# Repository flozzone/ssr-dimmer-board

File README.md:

# ssr-dimmer-board

Rebuild of https://github.com/fleshgordo/diskohedron using recent 
SSRs with source code for Arduino microcontroller.

## Hardware

* Schematic: https://github.com/flozzone/ssr-dimmer-board/blob/master/hw/schematic.pdf
* Layout: https://github.com/flozzone/ssr-dimmer-board/blob/master/hw/layout.pdf

## Building

    # prepare build framework
    cd src
    ./configure
    
    # building arduino v3.1 firmware
    cd bin-firmware
    make
    cd ..

    # building client library
    cd bin-client
    make
    cd ..
    
## Uploading

After having run through the building process you can upload the firmware
to the arduino. Be sure to attach the arduino with an USB cable to the 
workstation (It should be recognized as /dev/ttyUSB0).

    cd src/bin-firmware
    make upload
    
## Pin-Mapping

| Pin name 	| Description      	| Type (AVR side) 	| Arduino Pin   	| AVR Pin 	|
|----------	|------------------	|-----------------	|---------------	|---------	|
| ZC       	| Zero cross       	| INPUT           	| digital pin 2 	| PD2     	|
| CH1      	| Channel1 control 	| OUTPUT          	| digital pin 4 	| PD4     	|
| CH2      	| Channel2 control 	| OUTPUT          	| digital pin 5 	| PD5     	|
| CH3      	| Channel3 control 	| OUTPUT          	| digital pin 6 	| PD6     	|
| CH4      	| Channel4 control 	| OUTPUT          	| digital pin 7 	| PD7     	|
| CH5      	| Channel5 control 	| OUTPUT          	| digital pin 8 	| PB0     	|
| GND      	| Ground           	| POWER           	| GND           	| GND     	|

## Serial Protocol

The serial protocol consists of one single 5 byte message, which is described
in the following struct message. 

For the value argument of the message, currently only values between 0 and 16
are allowed.

    struct message {
      byte magic1 = 0xF6;
      byte magic2 = 0x6F;
      enum e_fire_type fire_type;
      enum e_channels channel_nr;
      byte value;
    };

    enum e_fire_type {
        NO_FIRE,
        PHASE_TRAILING_EDGE,
        PHASE_LEADING_EDGE,
        FULL_WAVE_BURST,
        HALF_WAVE_BURST
    };

    enum e_channels {
        CHANNEL1 = 0,
        CHANNEL2,
        CHANNEL3,
        CHANNEL4,
        CHANNEL5
    };

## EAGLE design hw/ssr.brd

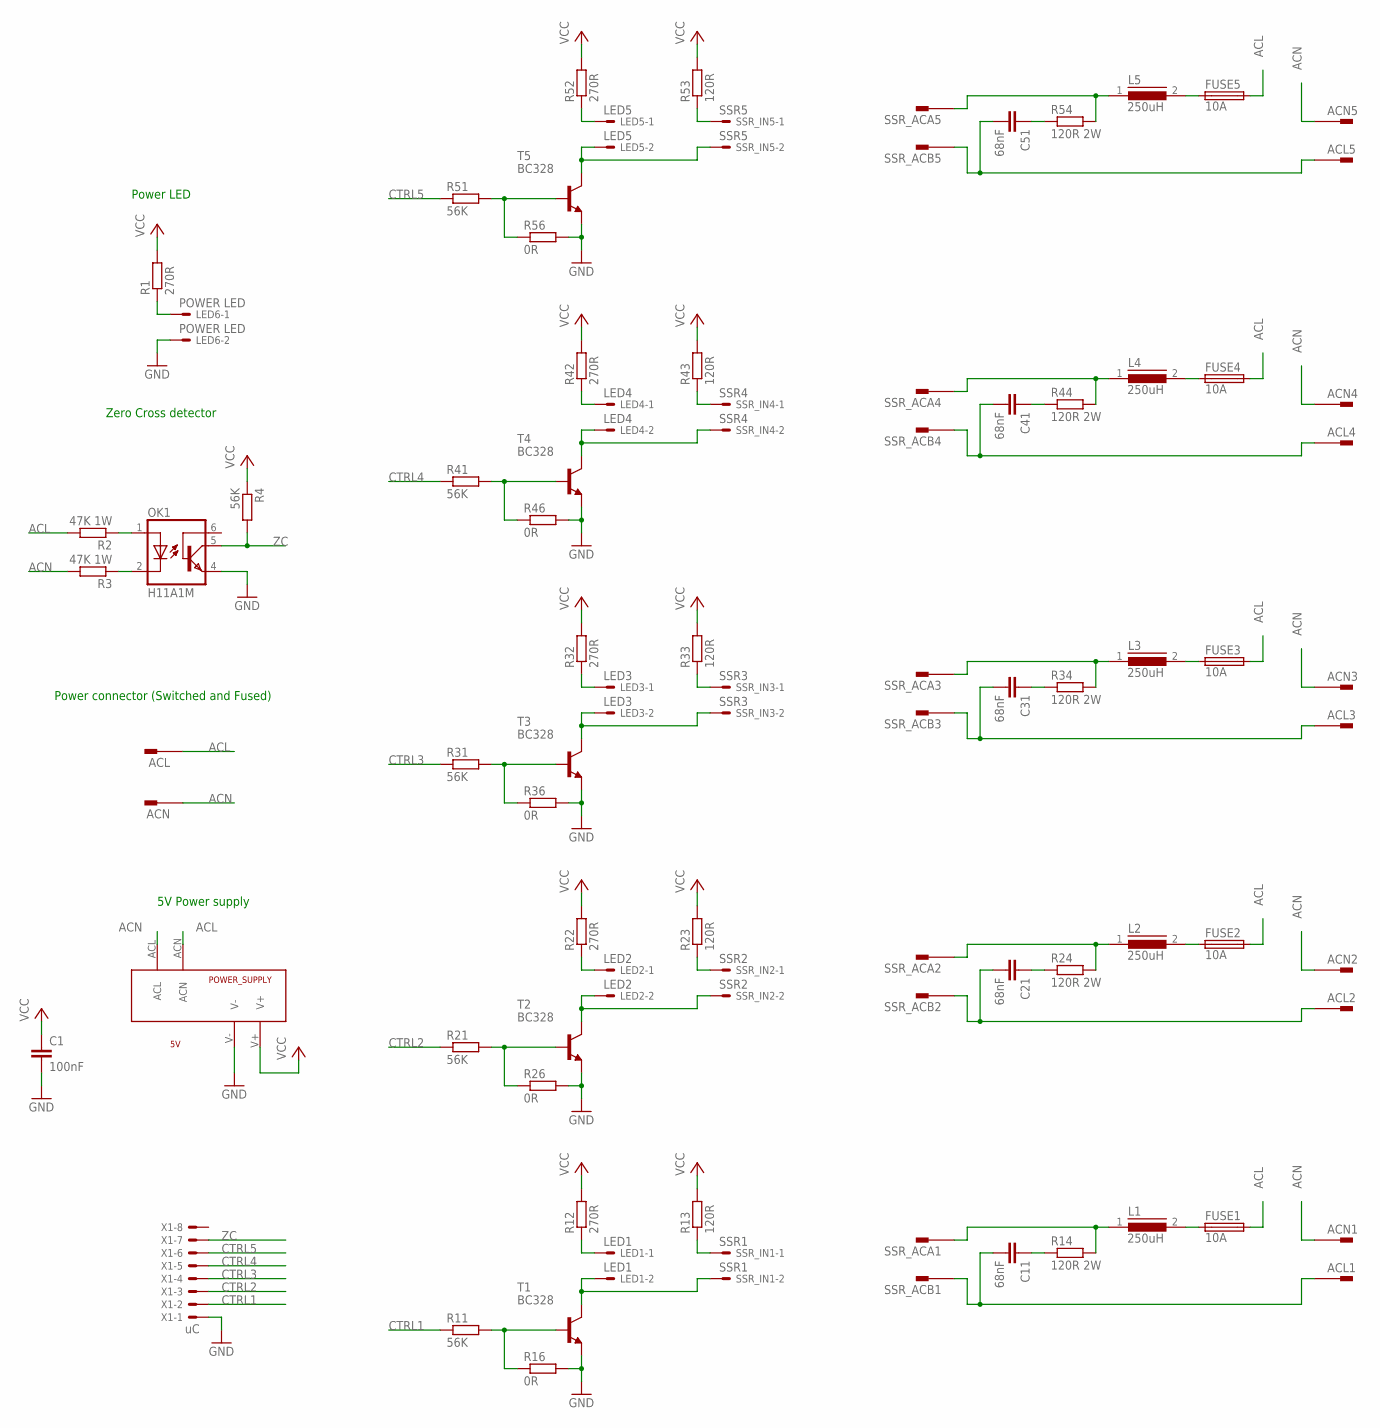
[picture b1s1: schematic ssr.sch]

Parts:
ACL, ACL1, ACL2, ACL3, ACL4, ACL5: PIN2F061.080; F061.080
ACN, ACN1, ACN2, ACN3, ACN4, ACN5: PIN2F061.080; F061.080
C1: 100nF; C2.5-2
C11, C21, C31, C41, C51: 68nF; C150-054X183
FUSE1, FUSE2, FUSE3, FUSE4, FUSE5: 10A; SH22,5
L1, L2, L3, L4, L5: 250uH; ATCA-08
LED1: LED1; KK-156-2
LED2: LED2; KK-156-2
LED3: LED3; KK-156-2
LED4: LED4; KK-156-2
LED5: LED5; KK-156-2
LED6: POWER LED; KK-156-2
OK1: H11A1M; DIL06
POWER_SUPPLY: 5V; SPN00205
R1, R12, R22, R32, R42, R52: 270R; 0207/10
R2, R3: 47K 1W; 0309/12
R4, R11, R21, R31, R41, R51: 56K; 0207/10
R13, R23, R33, R43, R53: 120R; 0207/10
R14, R24, R34, R44, R54: 120R 2W; 0617/22
R16, R26, R36, R46, R56: 0R; 0207/10
SSR_ACA1, SSR_ACA2, SSR_ACA3, SSR_ACA4, SSR_ACA5: PIN2F061.080; F061.080
SSR_ACB1, SSR_ACB2, SSR_ACB3, SSR_ACB4, SSR_ACB5: PIN2F061.080; F061.080
SSR_IN1: SSR1; KK-156-2
SSR_IN2: SSR2; KK-156-2
SSR_IN3: SSR3; KK-156-2
SSR_IN4: SSR4; KK-156-2
SSR_IN5: SSR5; KK-156-2
T1, T2, T3, T4, T5: BC328; TO92
X1: uC; KK-156-8

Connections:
ACL: ACL.1A, ACL.1B, FUSE1.2, FUSE2.2, FUSE3.2, FUSE4.2, FUSE5.2, POWER_SUPPLY.ACN, R2.2
ACN: ACN.1A, ACN.1B, ACN1.1A, ACN1.1B, ACN2.1A, ACN2.1B, ACN3.1A, ACN3.1B, ACN4.1A, ACN4.1B, ACN5.1A, ACN5.1B, POWER_SUPPLY.ACL, R3.2
CTRL1: R11.1, X1.2
CTRL2: R21.1, X1.3
CTRL3: R31.1, X1.4
CTRL4: R41.1, X1.5
CTRL5: R51.1, X1.6
GND: C1.2, LED6.2, OK1.4 (EMI), POWER_SUPPLY.V-, R16.2, R26.2, R36.2, R46.2, R56.2, T1.1 (E), T2.1 (E), T3.1 (E), T4.1 (E), T5.1 (E), X1.1
unnamed: LED1.2, SSR_IN1.2, T1.3 (C)
unnamed: LED1.1, R12.1
unnamed: R13.1, SSR_IN1.1
unnamed: R11.2, R16.1, T1.2 (B)
unnamed: C11.1, R14.1
unnamed: OK1.2 (C), R3.1
unnamed: OK1.1 (A), R2.1
unnamed: R23.1, SSR_IN2.1
unnamed: LED2.1, R22.1
unnamed: R21.2, R26.1, T2.2 (B)
unnamed: C21.1, R24.1
unnamed: LED2.2, SSR_IN2.2, T2.3 (C)
unnamed: R33.1, SSR_IN3.1
unnamed: LED3.1, R32.1
unnamed: R31.2, R36.1, T3.2 (B)
unnamed: C31.1, R34.1
unnamed: LED3.2, SSR_IN3.2, T3.3 (C)
unnamed: R43.1, SSR_IN4.1
unnamed: LED4.1, R42.1
unnamed: R41.2, R46.1, T4.2 (B)
unnamed: C41.1, R44.1
unnamed: LED4.2, SSR_IN4.2, T4.3 (C)
unnamed: R53.1, SSR_IN5.1
unnamed: LED5.1, R52.1
unnamed: R51.2, R56.1, T5.2 (B)
unnamed: C51.1, R54.1
unnamed: LED5.2, SSR_IN5.2, T5.3 (C)
unnamed: LED6.1, R1.1
unnamed: FUSE5.1, L5.2
unnamed: FUSE4.1, L4.2
unnamed: FUSE3.1, L3.2
unnamed: FUSE2.1, L2.2
unnamed: FUSE1.1, L1.2
SSR_ACA1: L1.1, R14.2, SSR_ACA1.1A, SSR_ACA1.1B
SSR_ACA2: L2.1, R24.2, SSR_ACA2.1A, SSR_ACA2.1B
SSR_ACA3: L3.1, R34.2, SSR_ACA3.1A, SSR_ACA3.1B
SSR_ACA4: L4.1, R44.2, SSR_ACA4.1A, SSR_ACA4.1B
SSR_ACA5: L5.1, R54.2, SSR_ACA5.1A, SSR_ACA5.1B
SSR_ACB1: ACL1.1A, ACL1.1B, C11.2, SSR_ACB1.1A, SSR_ACB1.1B
SSR_ACB2: ACL2.1A, ACL2.1B, C21.2, SSR_ACB2.1A, SSR_ACB2.1B
SSR_ACB3: ACL3.1A, ACL3.1B, C31.2, SSR_ACB3.1A, SSR_ACB3.1B
SSR_ACB4: ACL4.1A, ACL4.1B, C41.2, SSR_ACB4.1A, SSR_ACB4.1B
SSR_ACB5: ACL5.1A, ACL5.1B, C51.2, SSR_ACB5.1A, SSR_ACB5.1B
VCC: C1.1, POWER_SUPPLY.V+, R1.2, R4.1, R12.2, R13.2, R22.2, R23.2, R32.2, R33.2, R42.2, R43.2, R52.2, R53.2
ZC: OK1.5 (COL), R4.2, X1.7

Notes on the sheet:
Power connector (Switched and Fused)
5V Power supply
Zero Cross detector
Power LED

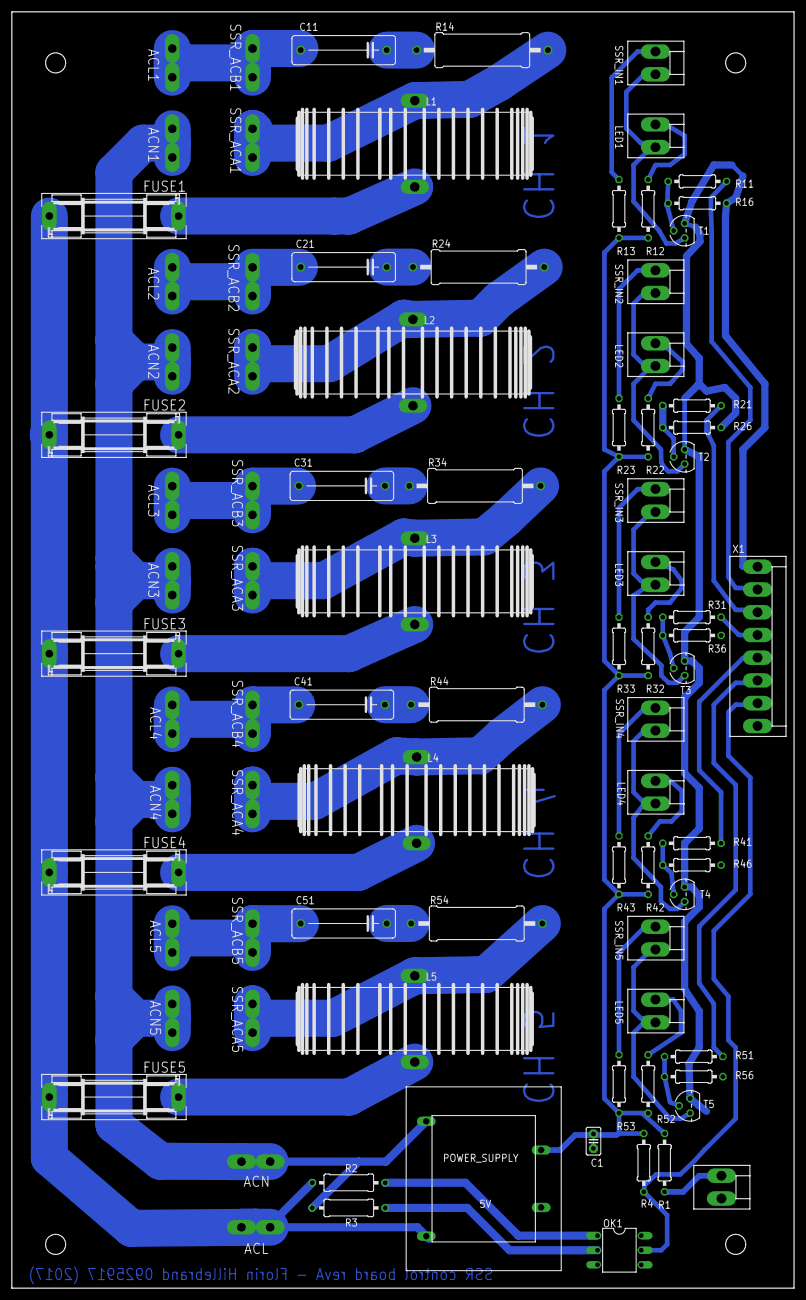
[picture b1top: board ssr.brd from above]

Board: 2 copper layers, 136.2 x 222.2 mm, 87 parts (0 on the bottom side), 53 nets.

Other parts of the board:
DRILEGEND: DRILEGEND

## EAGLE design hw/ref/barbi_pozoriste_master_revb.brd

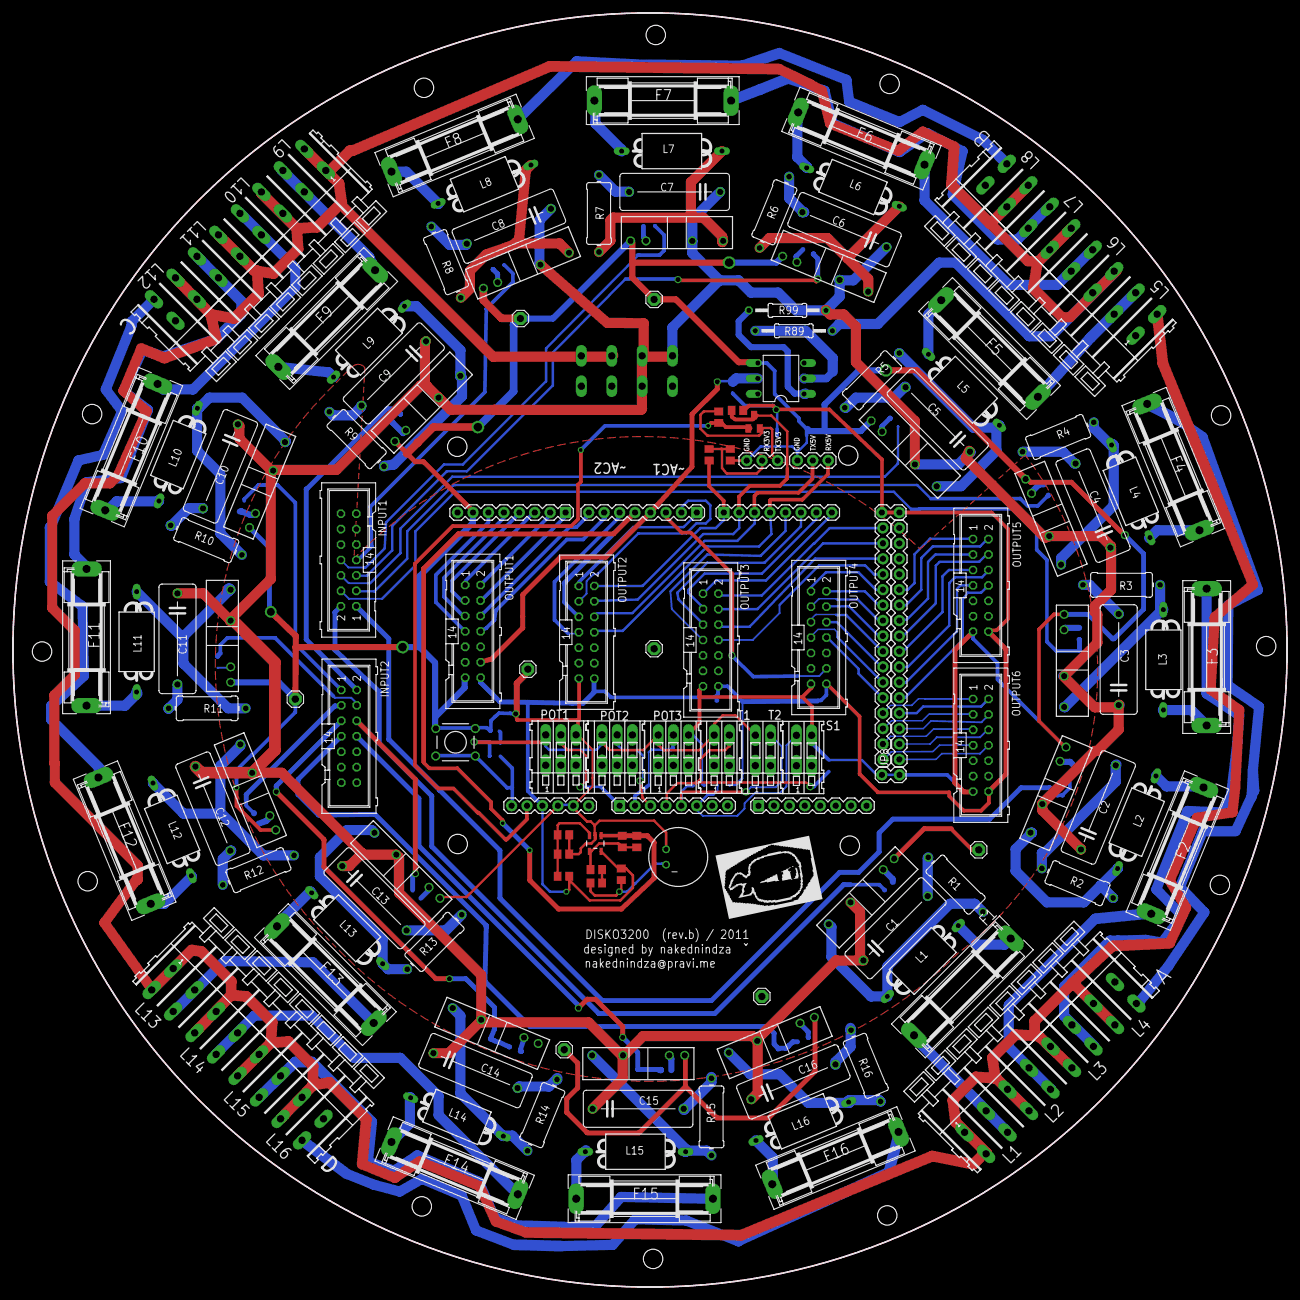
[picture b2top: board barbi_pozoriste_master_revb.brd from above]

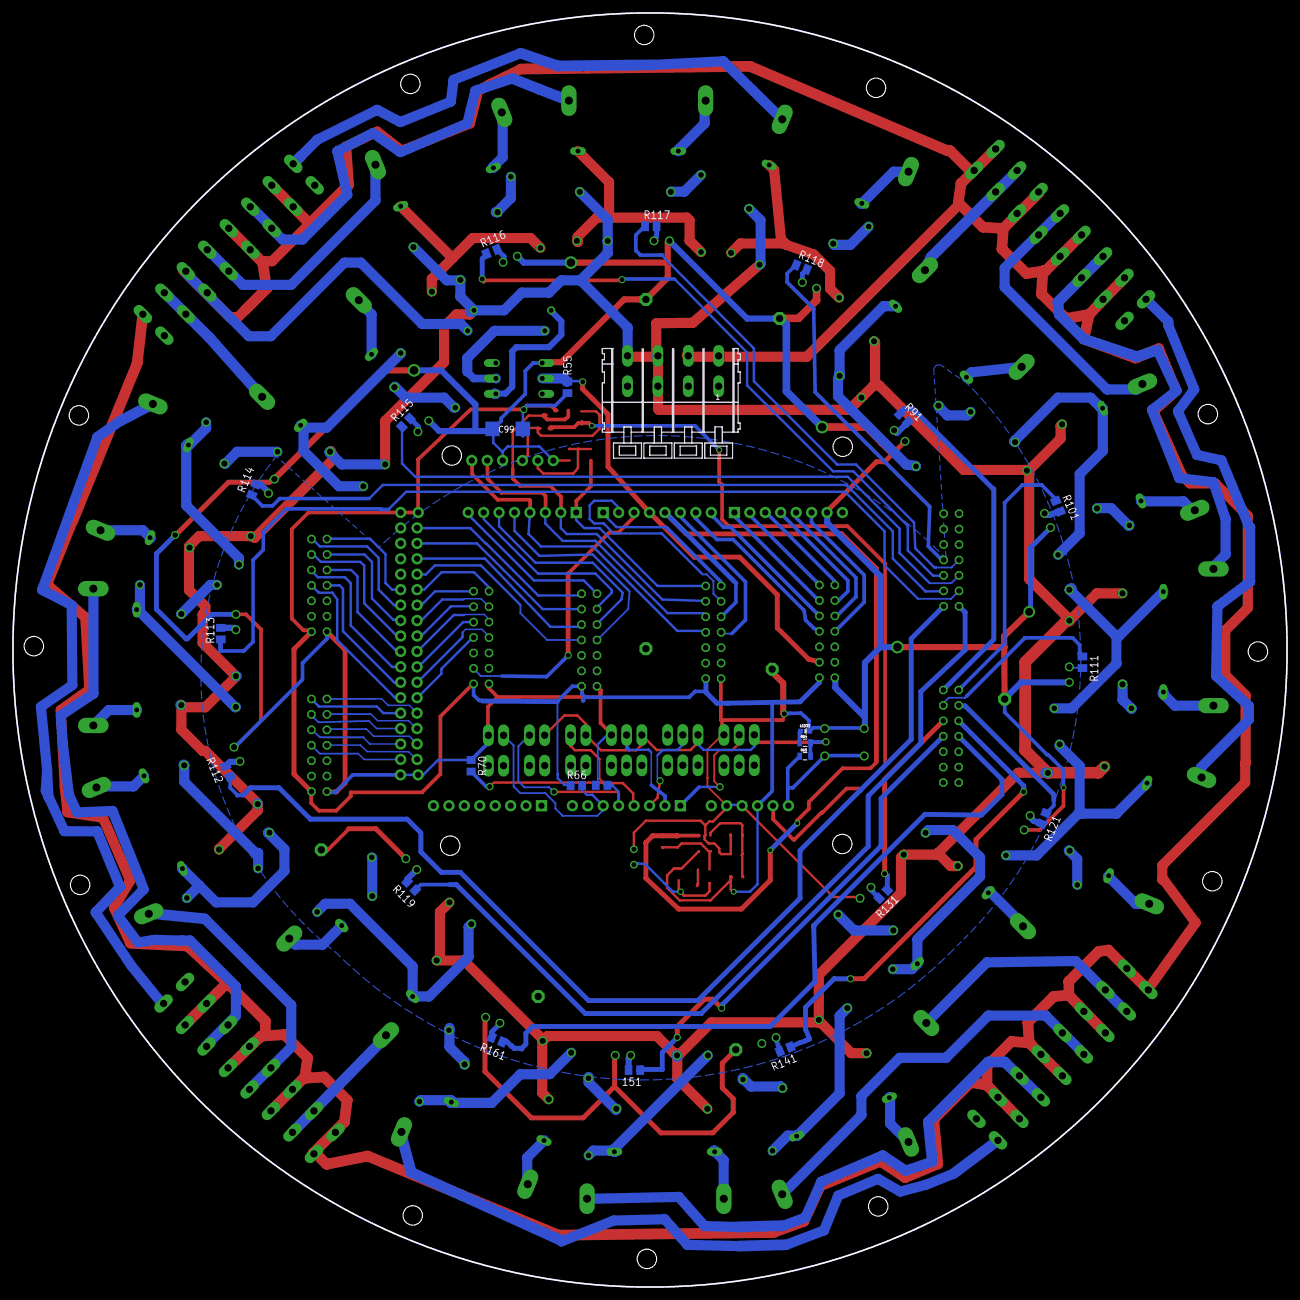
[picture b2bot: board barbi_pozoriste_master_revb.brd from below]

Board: 2 copper layers, 209.7 x 209.7 mm, 162 parts (25 on the bottom side), 168 nets.

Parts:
151: 330R; M0805
C1, C2, C3, C4, C5, C6, C7, C8, C9, C10, C11, C12, C13, C14, C15, C16: 68nF; C150-064X183
C17: 4.7uF; C0805
C18: 12pF; C0805
C19: 1uF; C0805
C99: 47uF; SMC_C
F1, F2, F3, F4, F5, F6, F7, F8, F9, F10, F11, F12, F13, F14, F15, F16: 3A; SH22,5
JP1, JP2: 1X03
JP3, JP4, JP5, JP6, JP7: 1X08
JP8, JP9: M16PTH; 1X16
JP10: 1X06
JP11, JP12: 1X02_LOCK
K1, K2, K3, K4, K5, K6, K7, K8, K9, K10, K11, K12, K13, K14, K15, K16: S202S01; S102S01
L1, L2, L3, L4, L5, L6, L7, L8, L9, L10, L11, L12, L13, L14, L15, L16: 300uH; ZD6-2W5
LED33: Red; LED-0603
LSP1, LSP2, LSP3, LSP4, LSP5, LSP6, LSP7, LSP8: MCS08
OK1: H11A1M; DIL06
Q1: BSS123; SOT23
R1, R2, R3, R4, R5, R6, R7, R8, R9, R10, R11, R12, R13, R14, R15, R16: 120R 2W; 0411/12
R17: 2k2; R0805
R18, R19, R20, R21, R22, R24, R25, R70, R71: 10k; R0805
R23: 1M; R0805
R55: 10k; M0805
R64: 330; 0805
R65: 10k; 0805
R66: 1k; R0805
R89, R99: 47k 1W; 0207/12
R91, R101, R111, R112, R113, R114, R115, R116, R117, R118, R119, R121, R131, R141, R161: 330R; M0805
S1: TACTILE-PTH
SV1, SV2, SV3, SV4, SV5, SV6, SV7, SV8: ML14
U$1: MIC9.7MM; MIC-9.7MM
U$2: OPA344; SOT23-5
X1: WAGO4-255-404-5; 255-404-5
X2, X3, X5, X6: WAGO8-255-408-5; 255-408-5
X10, X11, X12: 233-103
X13, X14, X15: 233-102

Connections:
3.3: JP10.2, Q1.1, R24.1
5V: R64.2, R65.2, X10.A1, X11.A1, X12.A1, X13.A1, X14.A1
A0: JP7.1, X10.A2
A1: JP7.2, X11.A2
A2: JP7.3, X12.A2
A3: JP7.4, R70.2, X13.A2
A4: JP7.5, R71.2, X14.A2
A5: JP7.6, R66.2, X15.A1
AC_NEUTRAL: R89.2, X1.B1, X1.B2, X2.B1, X2.B3, X2.B5, X2.B7, X3.B1, X3.B3, X3.B5, X3.B7, X5.B1, X5.B3, X5.B5, X5.B7, X6.B1, X6.B3, X6.B5, X6.B7
AC_PHASE: C1.1, C2.1, C3.1, C4.1, C5.1, C6.1, C7.1, C8.1, C9.1, C10.1, C11.1, C12.1, C13.1, C14.1, C15.1, C16.1, K1.2, K2.2, K3.2, K4.2, K5.2, K6.2, K7.2, K8.2, K9.2, K10.2, K11.2, K12.2, K13.2, K14.2, K15.2, K16.2, R99.2, X1.B3, X1.B4
D2: JP4.3, SV5.12
D3: JP4.4, OK1.5, R55.1, SV2.12
D4: C18.2, JP4.5, R23.1, SV3.5, U$2.1
D5: JP4.6, SV3.7
D6: JP4.7, SV2.8
D7: JP4.8, SV2.6
D8: JP3.1, SV2.4
D9: JP3.2, SV2.2
D10: JP3.3, SV2.1
D11: JP3.4, SV2.3
D12: JP3.5, SV2.5
D13: JP3.6, SV2.7
D14: JP5.1, R18.1, SV3.2
D15: JP5.2, Q1.3, R25.2, SV3.4
D16: JP1.2, JP5.3, SV3.6
D17: JP1.3, JP5.4, SV3.8
D18: JP5.5, SV4.7
D19: JP5.6, SV4.5
D22: JP9.16, SV4.2
D24: JP9.15, SV4.4
D26: JP9.14, SV4.6
D28: JP9.13, SV4.8
D30: JP9.12, SV5.1
D31: JP8.12, SV7.1
D32: JP9.11, SV5.2
D33: JP8.11, SV7.2
D34: JP9.10, SV5.3
D35: JP8.10, SV7.3
D36: JP9.9, SV5.4
D37: JP8.9, SV7.4
D38: JP9.8, SV5.5
D39: JP8.8, SV7.5
D40: JP9.7, SV5.6
D41: JP8.7, SV7.6
D42: JP9.6, SV5.7
D43: JP8.6, SV7.7
D44: JP9.5, SV5.8
D45: JP8.5, SV7.8
D46: JP9.4, SV6.1
D47: JP8.4, SV6.2
D48: JP9.3, SV6.3
D49: JP8.3, SV6.4
D50: JP9.2, SV6.5
D51: JP8.2, SV6.6
D52: JP9.1, SV6.7
D53: JP8.1, SV6.8
GND: C19.1, C99.-, JP1.1, JP2.1, JP3.7, JP10.4, JP10.5, JP11.1, JP11.2, K1.4, K2.4, K3.4, K4.4, K5.4, K6.4, K7.4, K8.4, K9.4, K10.4, K11.4, K12.4, K13.4, K14.4, K15.4, K16.4, LED33.C, LSP1.MP, LSP2.MP, LSP3.MP, LSP4.MP, LSP5.MP, LSP6.MP, LSP7.MP, LSP8.MP, OK1.4, R19.2, R22.1, R70.1, R71.1, S1.1, S1.2, SV2.13, SV3.13, SV4.13, SV5.13, SV6.13, SV7.13, U$1.1, U$2.2, X10.A3, X11.A3, X12.A3, X15.A2
INPUT1: R119.1, SV1.2
INPUT2: R112.1, SV1.1
INPUT3: R113.1, SV1.4
INPUT4: R114.1, SV1.3
INPUT5: R115.1, SV1.6
INPUT6: R116.1, SV1.5
INPUT7: R117.1, SV1.8
INPUT8: R118.1, SV1.7
INPUT9: R91.1, SV8.2
INPUT10: R101.1, SV8.1
INPUT11: R111.1, SV8.4
INPUT12: R121.1, SV8.3
INPUT13: R131.1, SV8.6
INPUT14: R141.1, SV8.5
INPUT15: 151.1, SV8.8
INPUT16: R161.1, SV8.7
LAMP1: F1.1, L1.2
LAMP2: F2.1, L2.2
LAMP3: F3.1, L3.2
LAMP4: F4.1, L4.2
LAMP5: F5.1, L5.2
LAMP6: F6.1, L6.2
LAMP7: F7.1, L7.2
LAMP8: F8.1, L8.2
LAMP9: F9.1, L9.2
LAMP10: F10.1, L10.2
LAMP11: F11.1, L11.2
LAMP12: F12.1, L12.2
LAMP13: F13.1, L13.2
LAMP14: F14.1, L14.2
LAMP15: F15.1, L15.2
LAMP16: F16.1, L16.2
unnamed: K2.1, L2.1, R2.2
unnamed: K1.1, L1.1, R1.1
unnamed: C1.2, R1.2
unnamed: C2.2, R2.1
unnamed: F4.2, X5.B8
unnamed: K3.1, L3.1, R3.2
unnamed: OK1.1, R99.1
unnamed: C3.2, R3.1
unnamed: F1.2, X5.B2
unnamed: F2.2, X5.B4
unnamed: C4.2, R4.1
unnamed: K4.1, L4.1, R4.2
unnamed: K5.1, L5.1, R5.2
unnamed: OK1.2, R89.1
unnamed: C5.2, R5.1
unnamed: F3.2, X5.B6
unnamed: K6.1, L6.1, R6.2
unnamed: C6.2, R6.1
unnamed: F5.2, X6.B2
unnamed: F8.2, X6.B8
unnamed: C7.2, R7.1
unnamed: K7.1, L7.1, R7.2
unnamed: K8.1, L8.1, R8.2
unnamed: C8.2, R8.1
unnamed: F7.2, X6.B6
unnamed: F6.2, X6.B4
unnamed: K2.3, R112.2
unnamed: K3.3, R113.2
unnamed: K4.3, R114.2
unnamed: K5.3, R115.2
unnamed: K6.3, R116.2
unnamed: K7.3, R117.2
unnamed: K8.3, R118.2
unnamed: K1.3, R119.2
unnamed: K10.3, R101.2
unnamed: K11.3, R111.2
unnamed: K12.3, R121.2
unnamed: K13.3, R131.2
unnamed: K14.3, R141.2
unnamed: 151.2, K15.3
unnamed: K16.3, R161.2
unnamed: K9.3, R91.2
unnamed: K9.1, L9.1, R9.1
unnamed: C9.2, R9.2
unnamed: K10.1, L10.1, R10.2
unnamed: C10.2, R10.1
unnamed: K11.1, L11.1, R11.2
unnamed: C11.2, R11.1
unnamed: C12.2, R12.1
unnamed: K12.1, L12.1, R12.2
unnamed: K13.1, L13.1, R13.2
unnamed: C13.2, R13.1
unnamed: K14.1, L14.1, R14.2
unnamed: C14.2, R14.1
unnamed: C15.2, R15.1
unnamed: K15.1, L15.1, R15.2
unnamed: K16.1, L16.1, R16.2
unnamed: C16.2, R16.1
unnamed: C17.1, R17.1, U$1.2
unnamed: C19.2, R21.1, R22.2, U$2.3
unnamed: C17.2, R20.2
unnamed: C18.1, R20.1, R23.2, U$2.4
unnamed: F12.2, X2.B8
unnamed: F9.2, X2.B2
unnamed: F10.2, X2.B4
unnamed: F11.2, X2.B6
unnamed: F13.2, X3.B2
unnamed: F16.2, X3.B8
unnamed: F15.2, X3.B6
unnamed: F14.2, X3.B4
unnamed: LED33.A, R64.1
RES: JP10.1, R65.1, S1.3, S1.4
RX0: JP4.1, SV3.1
RX3V3: JP2.2, R18.2, R19.1
SCL: JP5.8, SV4.1
SDA: JP5.7, SV4.3
TX1: JP4.2, SV3.3
TX3V3: JP2.3, Q1.2, R24.2
VCC: C99.+, JP10.3, JP12.1, JP12.2, R17.2, R21.2, R25.1, R55.2, R66.1, SV2.14, SV3.14, SV4.14, SV5.14, SV6.14, SV7.14, U$2.5

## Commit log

2017-01-18 Copy existing sources from local repo.
2017-01-18 Updating README.
2017-01-18 Cleanup and document.
2017-01-19 Put zero cross detection into a library.
2017-01-19 Remove obsolete build example.
2017-01-19 Start extending zero cross with capture B.
2017-01-19 Enable programming via cmake.
2017-01-19 Cleanup
2017-01-19 Remove debugging.
2017-01-19 Adapt calibration offset to new resistor values.
2017-01-19 Adapt schematic and board layout according to new parts.
2017-01-20 start with multichannel support.
2017-01-20 Export board layout files.
2017-02-19 Do dimming using 256 fractions per each half wave.
2017-02-19 hw: update PCB layout and outputs.
2017-02-19 fw: implement burst fire control using look-up table.
2017-02-19 fw: fix burst fire doing an additional cycle.
2017-02-19 fw: correctly remove a channel from the event list.
2017-02-19 fw: cleanup.
2017-02-23 update README.
2017-02-23 add comments for driver.
2017-10-06 cleanup.
2017-10-10 Add documentation for the serial protocol.
